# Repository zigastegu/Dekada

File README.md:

## Breadboard friendly Five Decade Programmable Resistor Board

more images inside version folders

### 0v3:

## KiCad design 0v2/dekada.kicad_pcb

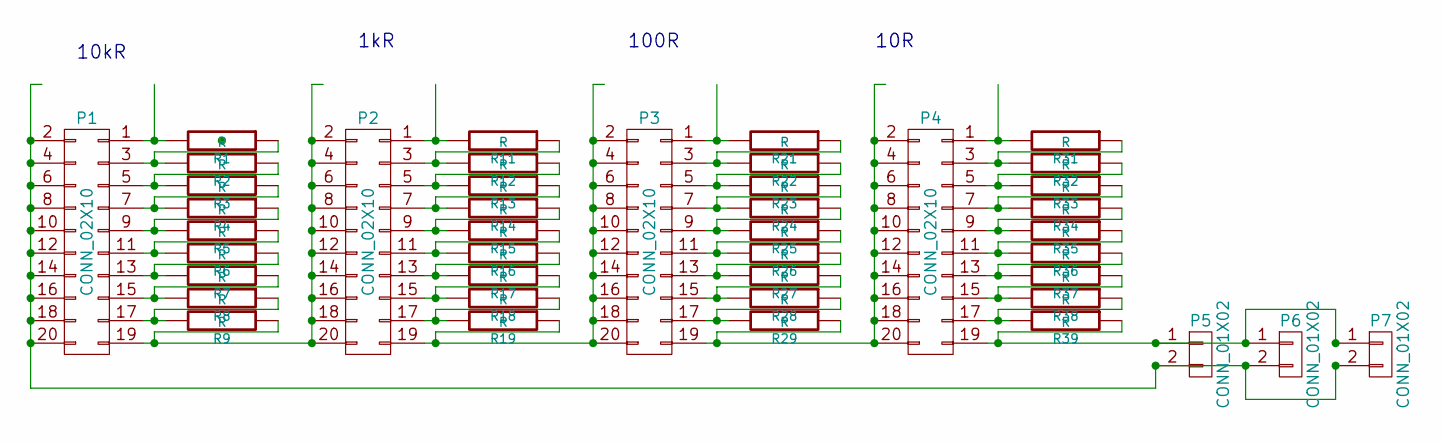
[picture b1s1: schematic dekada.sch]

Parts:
P1, P2, P3, P4: CONN_02X10; Pin_Header_Straight_2x10
P5, P6, P7: CONN_01X02; Pin_Header_Straight_1x02
R1, R2, R3, R4, R5, R6, R7, R8, R9, R11, R12, R13, R14, R15, R16, R17, R18, R19, R21, R22, R23, R24, R25, R26, R27, R28, R29, R31, R32, R33, R34, R35, R36, R37, R38, R39: R; R_1206_HandSoldering

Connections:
unnamed: P1.1, R1.2
unnamed: P1.3, R1.1, R2.2
unnamed: P1.5, R2.1, R3.2
unnamed: P1.7, R3.1, R4.2
unnamed: P1.9, R4.1, R5.2
unnamed: P1.2, P1.4, P1.6, P1.8, P1.10, P1.12, P1.14, P1.16, P1.18, P1.20, P5.2, P6.2, P7.2
unnamed: P1.11, R5.1, R6.2
unnamed: P1.13, R6.1, R7.2
unnamed: P1.15, R7.1, R8.2
unnamed: P1.17, R8.1, R9.2
unnamed: P1.19, P2.2, P2.4, P2.6, P2.8, P2.10, P2.12, P2.14, P2.16, P2.18, P2.20, R9.1
unnamed: P2.1, R11.2
unnamed: P2.3, R11.1, R12.2
unnamed: P2.5, R12.1, R13.2
unnamed: P2.7, R13.1, R14.2
unnamed: P2.9, R14.1, R15.2
unnamed: P2.11, R15.1, R16.2
unnamed: P2.13, R16.1, R17.2
unnamed: P2.15, R17.1, R18.2
unnamed: P2.17, R18.1, R19.2
unnamed: P2.19, P3.2, P3.4, P3.6, P3.8, P3.10, P3.12, P3.14, P3.16, P3.18, P3.20, R19.1
unnamed: P3.1, R21.2
unnamed: P3.3, R21.1, R22.2
unnamed: P3.5, R22.1, R23.2
unnamed: P3.7, R23.1, R24.2
unnamed: P3.9, R24.1, R25.2
unnamed: P3.11, R25.1, R26.2
unnamed: P3.13, R26.1, R27.2
unnamed: P3.15, R27.1, R28.2
unnamed: P3.17, R28.1, R29.2
unnamed: P3.19, P4.2, P4.4, P4.6, P4.8, P4.10, P4.12, P4.14, P4.16, P4.18, P4.20, R29.1
unnamed: P4.1, R31.2
unnamed: P4.3, R31.1, R32.2
unnamed: P4.5, R32.1, R33.2
unnamed: P4.7, R33.1, R34.2
unnamed: P4.9, R34.1, R35.2
unnamed: P4.11, R35.1, R36.2
unnamed: P4.13, R36.1, R37.2
unnamed: P4.15, R37.1, R38.2
unnamed: P4.17, R38.1, R39.2
unnamed: P4.19, P5.1, P6.1, P7.1, R39.1

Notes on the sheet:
10R
100R
1kR
10kR

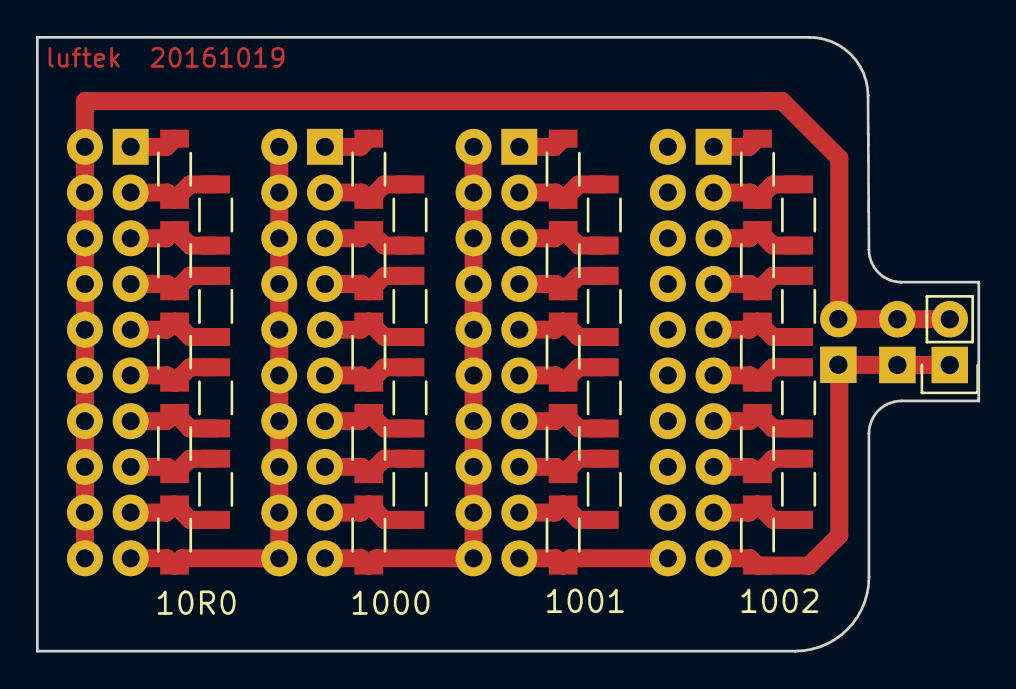
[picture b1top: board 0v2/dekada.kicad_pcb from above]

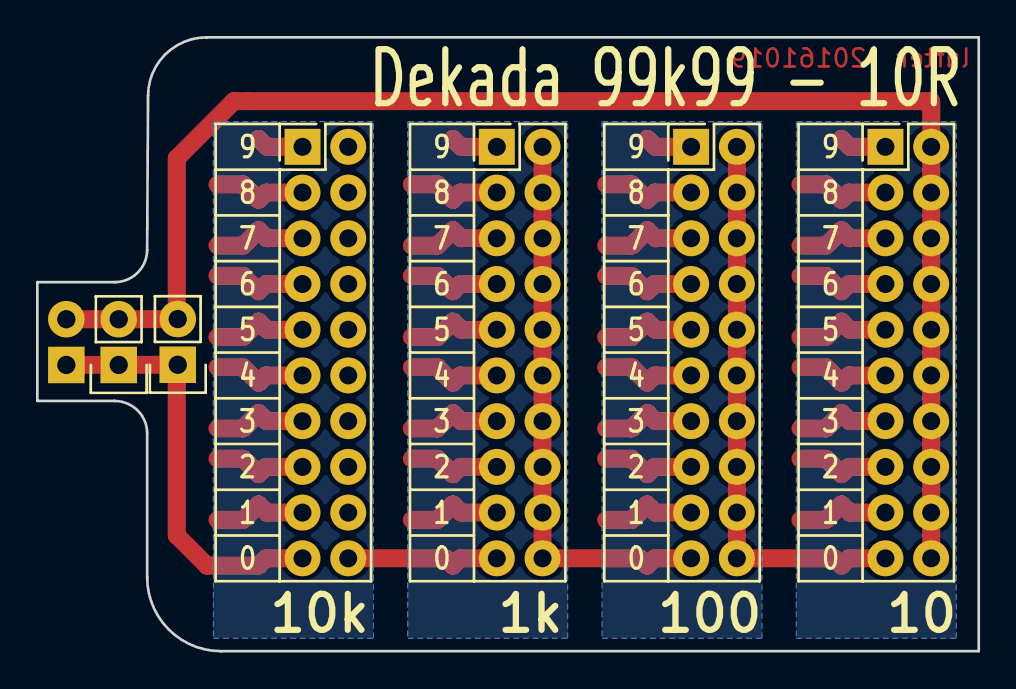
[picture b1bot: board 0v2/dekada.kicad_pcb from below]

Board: 2 copper layers, 52.3 x 34.1 mm, 43 parts (6 on the bottom side), 41 nets.

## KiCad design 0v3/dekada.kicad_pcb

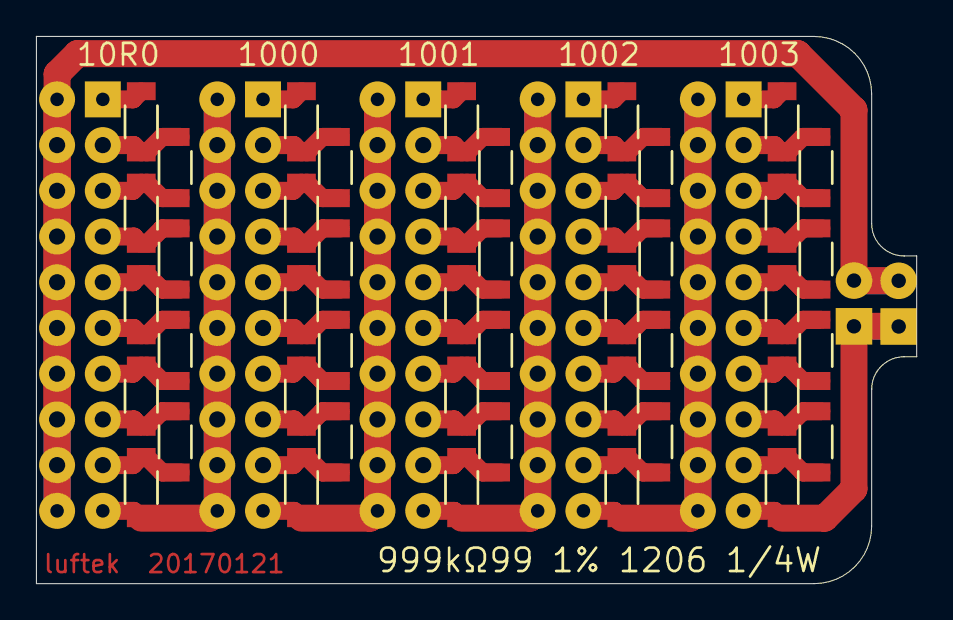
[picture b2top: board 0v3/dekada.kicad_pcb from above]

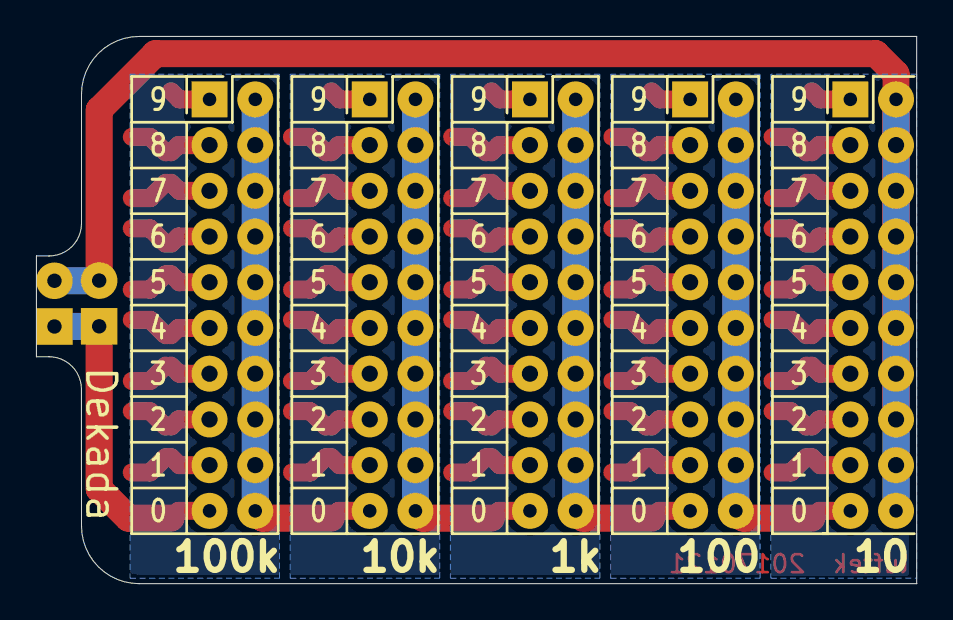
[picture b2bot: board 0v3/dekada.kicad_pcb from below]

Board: 2 copper layers, 48.9 x 30.4 mm, 52 parts (7 on the bottom side), 51 nets.

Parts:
P1, P2: CONN_01X02; Pin_Header_Straight_1x02
P3, P4, P5, P6, P7: CONN_02X10; Pin_Header_Straight_2x10_Custom
R1, R2, R3, R4, R5, R6, R7, R8, R9, R10, R11, R12, R13, R14, R15, R16, R17, R18, R19, R20, R21, R22, R23, R24, R25, R26, R27, R28, R29, R30, R31, R32, R33, R34, R35, R36, R37, R38, R39, R40, R41, R42, R43, R44, R45: R; R_1206_Custom

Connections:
/1k_dekada/comm_1: P5.19, P6.2, P6.4, P6.6, P6.8, P6.10, P6.12, P6.14, P6.16, P6.18, P6.20, R27.1
/10_dekada/comm_1: P3.19, P4.2, P4.4, P4.6, P4.8, P4.10, P4.12, P4.14, P4.16, P4.18, P4.20, R9.1
/10_dekada/comm_2: P1.2, P2.2, P3.2, P3.4, P3.6, P3.8, P3.10, P3.12, P3.14, P3.16, P3.18, P3.20
/10k_dekada/comm_1: P6.19, P7.2, P7.4, P7.6, P7.8, P7.10, P7.12, P7.14, P7.16, P7.18, P7.20, R36.1
/100_dekada/comm_1: P4.19, P5.2, P5.4, P5.6, P5.8, P5.10, P5.12, P5.14, P5.16, P5.18, P5.20, R18.1
/100k_dekada/comm_1: P1.1, P2.1, P7.19, R45.1
unnamed: P3.1, R1.2
unnamed: P3.3, R1.1, R2.2
unnamed: P3.5, R2.1, R3.2
unnamed: P3.7, R3.1, R4.2
unnamed: P3.9, R4.1, R5.2
unnamed: P3.11, R5.1, R6.2
unnamed: P3.13, R6.1, R7.2
unnamed: P3.15, R7.1, R8.2
unnamed: P3.17, R8.1, R9.2
unnamed: P4.1, R10.2
unnamed: P4.3, R10.1, R11.2
unnamed: P4.5, R11.1, R12.2
unnamed: P4.7, R12.1, R13.2
unnamed: P4.9, R13.1, R14.2
unnamed: P4.11, R14.1, R15.2
unnamed: P4.13, R15.1, R16.2
unnamed: P4.15, R16.1, R17.2
unnamed: P4.17, R17.1, R18.2
unnamed: P5.1, R19.2
unnamed: P5.3, R19.1, R20.2
unnamed: P5.5, R20.1, R21.2
unnamed: P5.7, R21.1, R22.2
unnamed: P5.9, R22.1, R23.2
unnamed: P5.11, R23.1, R24.2
unnamed: P5.13, R24.1, R25.2
unnamed: P5.15, R25.1, R26.2
unnamed: P5.17, R26.1, R27.2
unnamed: P6.1, R28.2
unnamed: P6.3, R28.1, R29.2
unnamed: P6.5, R29.1, R30.2
unnamed: P6.7, R30.1, R31.2
unnamed: P6.9, R31.1, R32.2
unnamed: P6.11, R32.1, R33.2
unnamed: P6.13, R33.1, R34.2
unnamed: P6.15, R34.1, R35.2
unnamed: P6.17, R35.1, R36.2
unnamed: P7.1, R37.2
unnamed: P7.3, R37.1, R38.2
unnamed: P7.5, R38.1, R39.2
unnamed: P7.7, R39.1, R40.2
unnamed: P7.9, R40.1, R41.2
unnamed: P7.11, R41.1, R42.2
unnamed: P7.13, R42.1, R43.2
unnamed: P7.15, R43.1, R44.2
unnamed: P7.17, R44.1, R45.2

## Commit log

2016-10-19 :neckbeard: Added .gitattributes & .gitignore files
2016-10-19 Initial commit
    Breadboard friendly Four Decade Programmable Resistor Board, 1%, 1/4W
2016-10-19 ebay link
2016-10-19 Revert "ebay link"
    This reverts commit 7c79750c705ca72fe43883e8d1787d41362d8c0b.
2016-10-19 jao jao, stupido
2017-04-22 Version 0v3
    assembled, tested, working
    no downsides or need for improvement found for now
